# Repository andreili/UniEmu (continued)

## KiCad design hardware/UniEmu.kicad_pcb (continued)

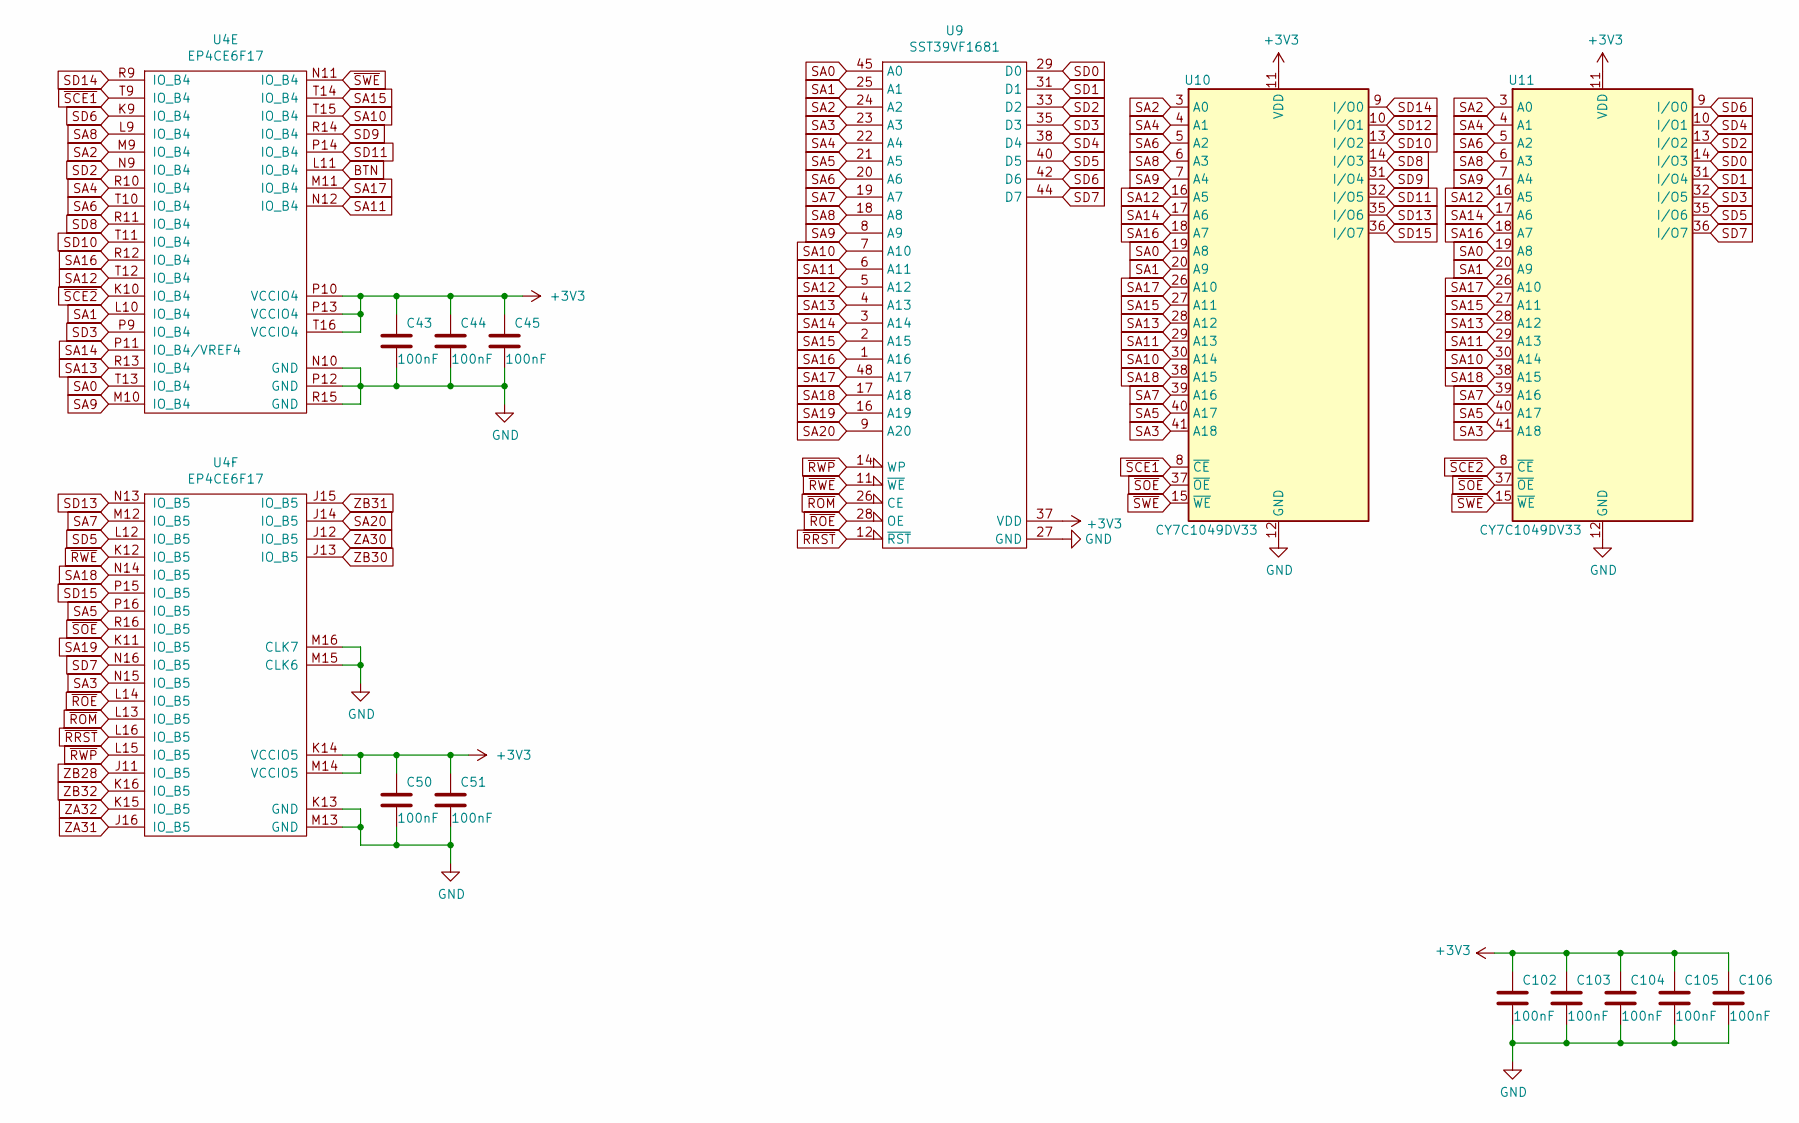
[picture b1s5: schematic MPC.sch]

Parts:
C43, C44, C45, C50, C51, C102, C103, C104, C105, C106: 100nF; C_0805_2012Metric
U4: EP4CE6F17; BGA-256_17.0x17.0mm_Layout16x16_P1.0mm_Ball0.5mm_Pad0.4mm_N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
U9: SST39VF1681; TSOP-I-48_18.4x12mm_P0.5mm
U10, U11: CY7C1049DV33; TSOP-II-44_10.16x18.41mm_P0.8mm

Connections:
BTN: U4.L11 (IO_B4); also elsewhere on the board
GND: C43.2, C44.2, C45.2, C50.2, C51.2, C102.2, C103.2, C104.2, C105.2, C106.2, U4.K13 (GND), U4.M13 (GND), U4.M15 (CLK6), U4.M16 (CLK7), U4.N10 (GND), U4.P12 (GND), U4.R15 (GND), U9.27 (GND), U10.12 (GND), U10.34 (GND), U11.12 (GND), U11.34 (GND); also elsewhere on the board
SA0: U4.T13 (IO_B4), U9.45 (A0), U10.19 (A8), U11.19 (A8)
SA1: U4.L10 (IO_B4), U9.25 (A1), U10.20 (A9), U11.20 (A9)
SA2: U4.M9 (IO_B4), U9.24 (A2), U10.3 (A0), U11.3 (A0)
SA3: U4.N15 (IO_B5), U9.23 (A3), U10.41 (A18), U11.41 (A18)
SA4: U4.R10 (IO_B4), U9.22 (A4), U10.4 (A1), U11.4 (A1)
SA5: U4.P16 (IO_B5), U9.21 (A5), U10.40 (A17), U11.40 (A17)
SA6: U4.T10 (IO_B4), U9.20 (A6), U10.5 (A2), U11.5 (A2)
SA7: U4.M12 (IO_B5), U9.19 (A7), U10.39 (A16), U11.39 (A16)
SA8: U4.L9 (IO_B4), U9.18 (A8), U10.6 (A3), U11.6 (A3)
SA9: U4.M10 (IO_B4), U9.8 (A9), U10.7 (A4), U11.7 (A4)
SA10: U4.T15 (IO_B4), U9.7 (A10), U10.30 (A14), U11.30 (A14)
SA11: U4.N12 (IO_B4), U9.6 (A11), U10.29 (A13), U11.29 (A13)
SA12: U4.T12 (IO_B4), U9.5 (A12), U10.16 (A5), U11.16 (A5)
SA13: U4.R13 (IO_B4), U9.4 (A13), U10.28 (A12), U11.28 (A12)
SA14: U4.P11 (IO_B4/VREF4), U9.3 (A14), U10.17 (A6), U11.17 (A6)
SA15: U4.T14 (IO_B4), U9.2 (A15), U10.27 (A11), U11.27 (A11)
SA16: U4.R12 (IO_B4), U9.1 (A16), U10.18 (A7), U11.18 (A7)
SA17: U4.M11 (IO_B4), U9.48 (A17), U10.26 (A10), U11.26 (A10)
SA18: U4.N14 (IO_B5), U9.17 (A18), U10.38 (A15), U11.38 (A15)
SA19: U4.K11 (IO_B5), U9.16 (A19)
SA20: U4.J14 (IO_B5), U9.9 (A20)
SD0: U9.29 (D0), U11.14 (I/O3); also elsewhere on the board
SD1: U9.31 (D1), U11.31 (I/O4); also elsewhere on the board
SD2: U4.N9 (IO_B4), U9.33 (D2), U11.13 (I/O2)
SD3: U4.P9 (IO_B4), U9.35 (D3), U11.32 (I/O5)
SD4: U9.38 (D4), U11.10 (I/O1); also elsewhere on the board
SD5: U4.L12 (IO_B5), U9.40 (D5), U11.35 (I/O6)
SD6: U4.K9 (IO_B4), U9.42 (D6), U11.9 (I/O0)
SD7: U4.N16 (IO_B5), U9.44 (D7), U11.36 (I/O7)
SD8: U4.R11 (IO_B4), U10.14 (I/O3)
SD9: U4.R14 (IO_B4), U10.31 (I/O4)
SD10: U4.T11 (IO_B4), U10.13 (I/O2)
SD11: U4.P14 (IO_B4), U10.32 (I/O5)
SD12: U10.10 (I/O1); also elsewhere on the board
SD13: U4.N13 (IO_B5), U10.35 (I/O6)
SD14: U4.R9 (IO_B4), U10.9 (I/O0)
SD15: U4.P15 (IO_B5), U10.36 (I/O7)
VREF: C43.1, C44.1, C45.1, C50.1, C51.1, C102.1, C103.1, C104.1, C105.1, C106.1, U4.K14 (VCCIO5), U4.M14 (VCCIO5), U4.P10 (VCCIO4), U4.P13 (VCCIO4), U4.T16 (VCCIO4), U9.37 (VDD), U10.11 (VDD), U10.33 (VDD), U11.11 (VDD), U11.33 (VDD); also elsewhere on the board
ZA30: U4.J12 (IO_B5); also elsewhere on the board
ZA31: U4.J16 (IO_B5); also elsewhere on the board
ZA32: U4.K15 (IO_B5); also elsewhere on the board
ZB28: U4.J11 (IO_B5); also elsewhere on the board
ZB30: U4.J13 (IO_B5); also elsewhere on the board
ZB31: U4.J15 (IO_B5); also elsewhere on the board
ZB32: U4.K16 (IO_B5); also elsewhere on the board
~ROE: U4.L14 (IO_B5), U9.28 (OE)
~ROM: U4.L13 (IO_B5), U9.26 (CE)
~RRST: U4.L16 (IO_B5), U9.12 (~RST)
~RWE: U4.K12 (IO_B5), U9.11 (~WE)
~RWP: U4.L15 (IO_B5), U9.14 (WP)
~SCE1: U4.T9 (IO_B4), U10.8 (~CE)
~SCE2: U4.K10 (IO_B4), U11.8 (~CE)
~SOE: U4.R16 (IO_B5), U10.37 (~OE), U11.37 (~OE)
~SWE: U4.N11 (IO_B4), U10.15 (~WE), U11.15 (~WE)

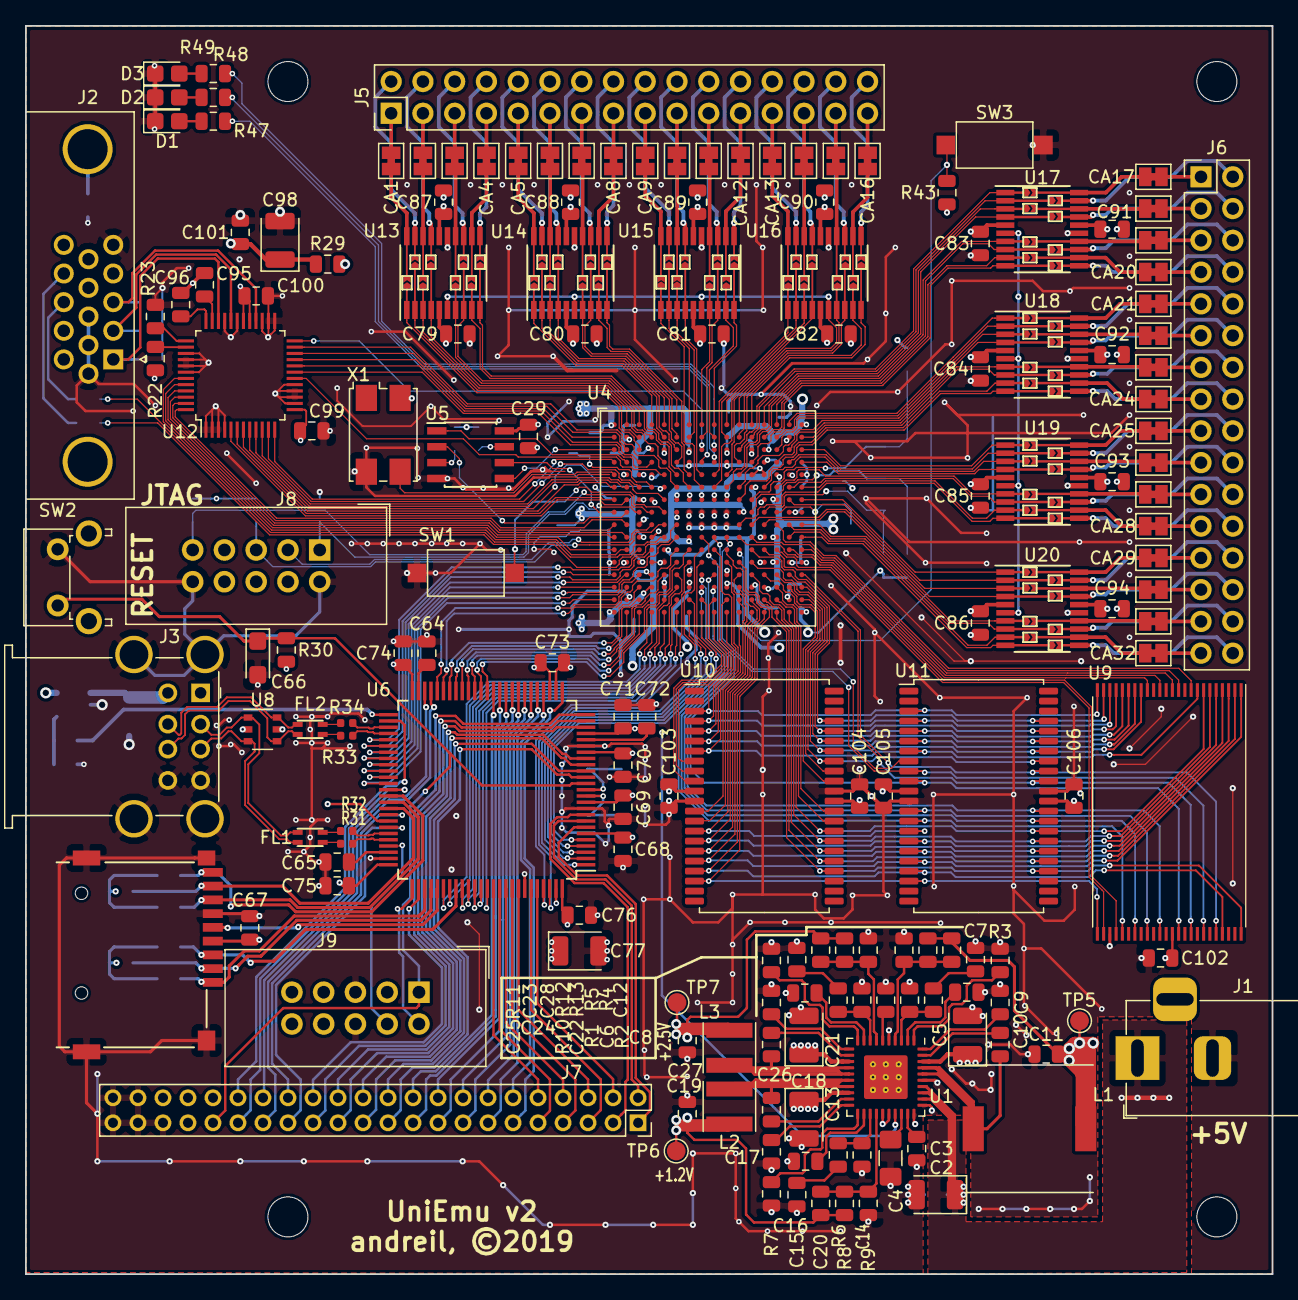
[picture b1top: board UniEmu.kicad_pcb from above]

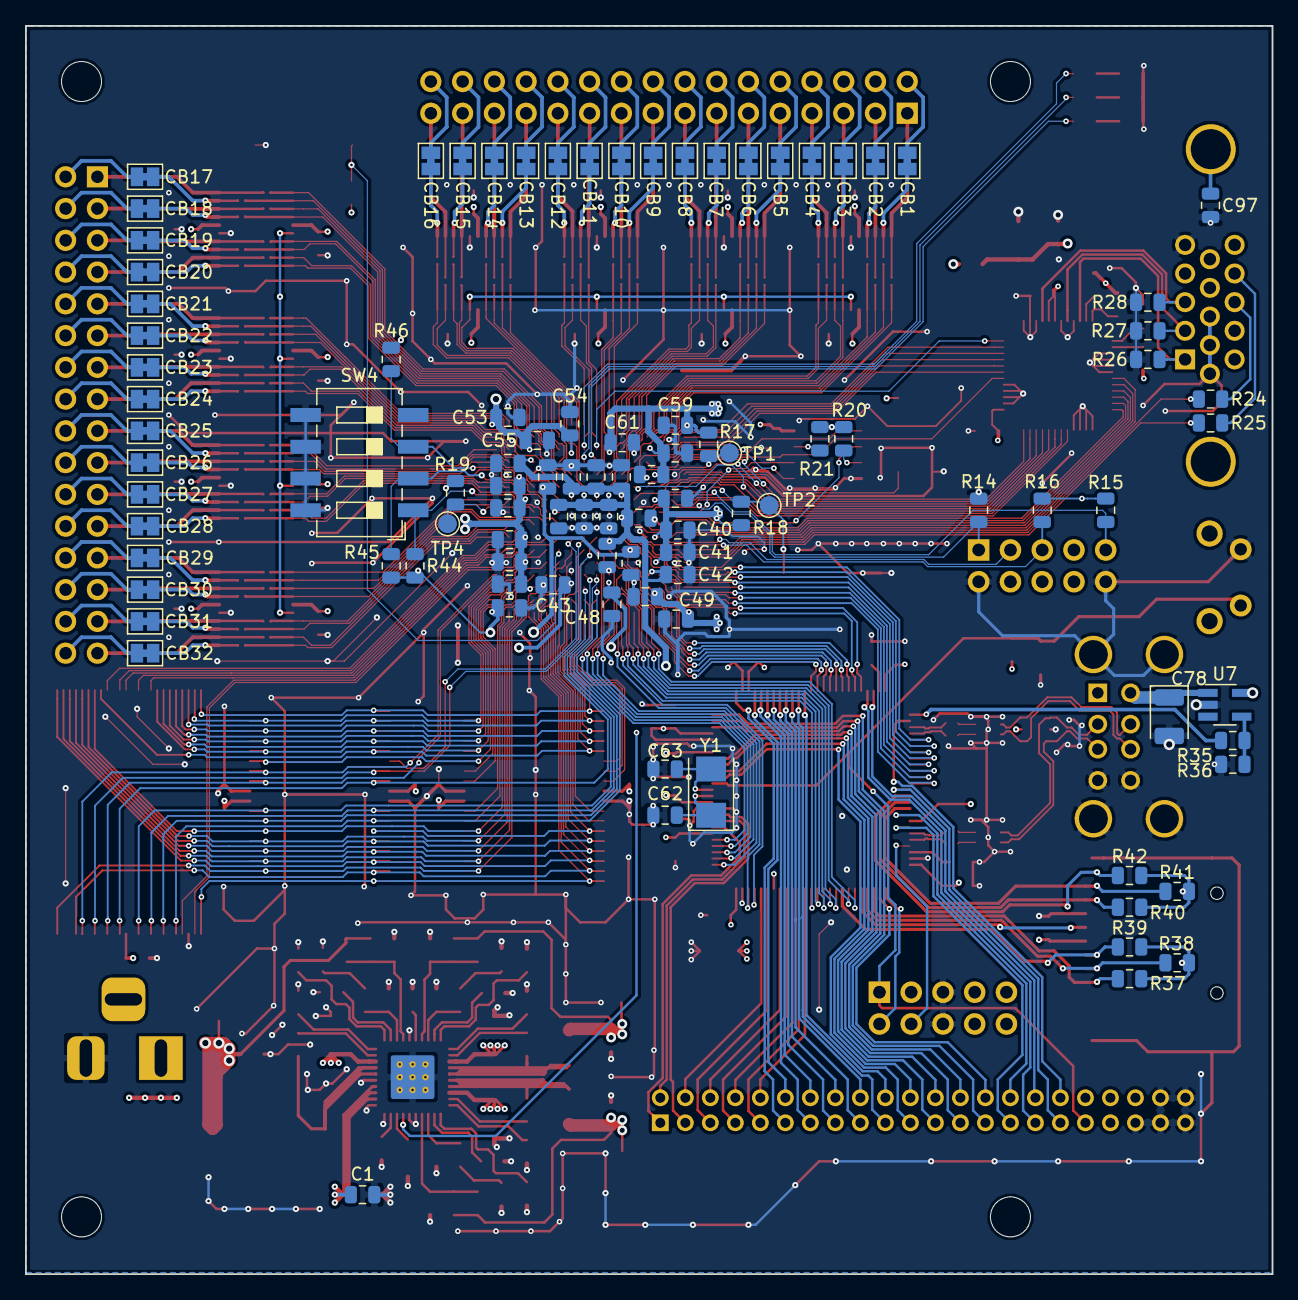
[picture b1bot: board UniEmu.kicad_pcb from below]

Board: 4 copper layers, 99.7 x 99.8 mm, 330 parts (99 on the bottom side), 423 nets.

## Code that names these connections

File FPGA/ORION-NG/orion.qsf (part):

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set_location_assignment PIN_A9 -to ZB[12]
set_location_assignment PIN_B9 -to ZA[12]
set_location_assignment PIN_K12 -to rwe_n
set_location_assignment PIN_N11 -to SWE
set_location_assignment PIN_R16 -to SOE
set_location_assignment PIN_T9 -to SCE[1]
set_location_assignment PIN_L14 -to roe_n
set_instance_assignment -name IO_STANDARD "3.3-V LVCMOS" -to B[0]
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set_location_assignment PIN_A3 -to ZB[3]
set_location_assignment PIN_E6 -to ZA[4]
set_location_assignment PIN_B5 -to ZB[5]
set_location_assignment PIN_C8 -to VCLK
set_location_assignment PIN_E10 -to ZOE
set_location_assignment PIN_F11 -to ZB[22]
set_location_assignment PIN_C14 -to ZA[22]
set_location_assignment PIN_C16 -to ZA[25]
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set_location_assignment PIN_T15 -to SA[10]
set_location_assignment PIN_R14 -to SD[9]
set_location_assignment PIN_P14 -to SD[11]
set_location_assignment PIN_L11 -to BTN
set_location_assignment PIN_M11 -to SA[17]
set_location_assignment PIN_N12 -to SA[11]
set_location_assignment PIN_N13 -to SD[13]
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
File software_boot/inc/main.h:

#ifndef MAIN_H
#define MAIN_H

#include "stm32_inc.h"
#include "xprintf.h"
#include "updater.h"
#include "sddriver.h"
#include "mscdriver.h"
#ifdef STM32_USE_USBH_HID
    #include "usbh_hid.h"
#endif //STM32_USE_USBH_HID
#ifdef STM32_USE_USBH_MSC
    #include "usbh_msc.h"
#endif //STM32_USE_USBH_MSC

#define LED_PORT gpiob
#define LED1_PIN STM32_GPIO::PIN_3
#define LED2_PIN STM32_GPIO::PIN_4
#define LED3_PIN STM32_GPIO::PIN_5

#define UART uart3

extern void (*main_fw_jump)(void);

#ifdef STM32_USE_USB
extern TCHAR msc_path[2][4];
extern FATFS MSCFatFS[2];
extern MSCDriver msc_driver[2];
#endif
#ifdef STM32_USE_SD
extern TCHAR SD_path[4];
extern SDDriver sd_driver;
extern FATFS SDFatFS;
#endif

#ifdef STM32_USE_USB
extern USBH_MSC usbh_msc[2];
#endif

typedef OS::process<OS::pr2, 1024> TProcWorker;
#ifndef STM32_USE_USB
typedef OS::process<OS::pr1, 1024> TProcUSBNULL;
extern TProcUSBNULL ProcUSBNULL;
#endif
extern TProcWorker ProcWorker;

void USBH_init();
void FAT_init();

#endif //MAIN_H

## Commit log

2019-04-28 Inital commit
2019-04-28 Add gitignore
2019-04-28 Bootloader sources added
2019-05-24 Обновлен загрузчик
2019-05-24 Обновлена схема:
    1. Исправлена нумерация CS SRAM;
    2. Исправлена нумерация сигналов для светодиодов.
2019-05-24 Добавлена заготовка основной прошивки
2019-05-24 Обновлён .gitignore
2019-05-24 Добавлена черновая версия реализации ORION-NG
2019-05-24 Исправлен переход на основную прошивку
2019-05-25 Bootloader: Исправлено для условной компиляции без USB.
2019-05-26 Обновлён загрузчик
2019-05-26 Добавлены отсутствующие файлы
2019-05-26 Исправлена процедура обновления прошивки
2019-05-26 Исправлено переключение контекста при переходе на основную прошивку
2019-06-05 Из загрузчика убрана поддрежка USBH HID - требовалось для тестов
